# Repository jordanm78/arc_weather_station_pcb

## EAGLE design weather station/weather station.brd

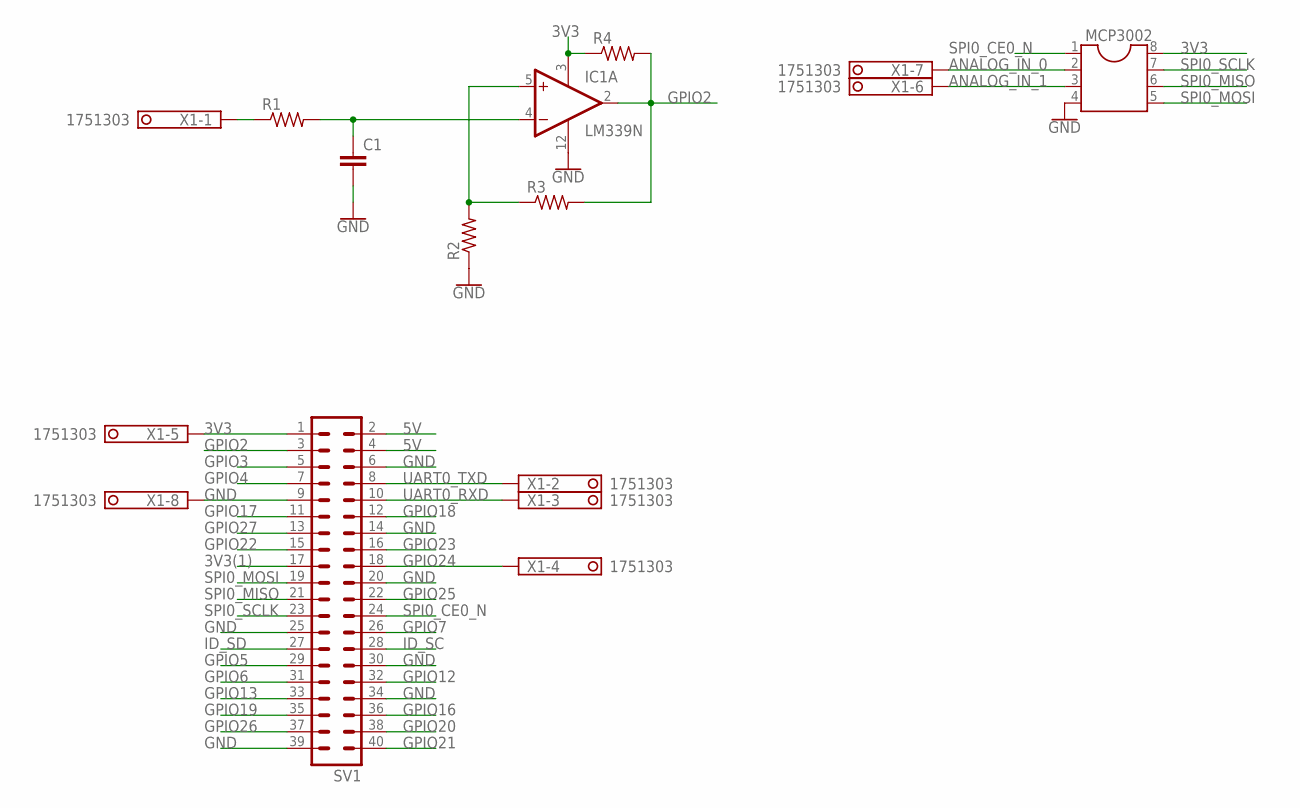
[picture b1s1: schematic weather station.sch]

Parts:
C1: C7.5/4; C7.5B4
IC1: LM339N; DIL14
MCP3002: DIL8S; SOCKET-08
R1, R2, R3, R4: R-US_0207/10; 0207/10
SV1: MA20-2
X1: 1751303

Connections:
3V3: IC1.3 (V+), MCP3002.8, R4.1, SV1.1, X1.5
3V3(1): SV1.17
5V: SV1.2, SV1.4
ANALOG_IN_0: MCP3002.2, X1.7
ANALOG_IN_1: MCP3002.3, X1.6
GND: C1.2, IC1.12 (GND), MCP3002.4, R2.1, SV1.6, SV1.9, SV1.14, SV1.20, SV1.25, SV1.30, SV1.34, SV1.39, X1.8
GPIO2: IC1.2 (OUT), R3.2, R4.2, SV1.3
GPIO3: SV1.5
GPIO4: SV1.7
GPIO5: SV1.29
GPIO6: SV1.31
GPIO7: SV1.26
GPIO12: SV1.32
GPIO13: SV1.33
GPIO16: SV1.36
GPIO17: SV1.11
GPIO18: SV1.12
GPIO19: SV1.35
GPIO20: SV1.38
GPIO21: SV1.40
GPIO22: SV1.15
GPIO23: SV1.16
GPIO24: SV1.18, X1.4
GPIO25: SV1.22
GPIO26: SV1.37
GPIO27: SV1.13
ID_SC: SV1.28
ID_SD: SV1.27
unnamed: C1.1, IC1.4 (-IN), R1.2
unnamed: IC1.5 (+IN), R2.2, R3.1
unnamed: R1.1, X1.1
SPI0_CE0_N: MCP3002.1, SV1.24
SPI0_MISO: MCP3002.6, SV1.21
SPI0_MOSI: MCP3002.5, SV1.19
SPI0_SCLK: MCP3002.7, SV1.23
UART0_RXD: SV1.10, X1.3
UART0_TXD: SV1.8, X1.2

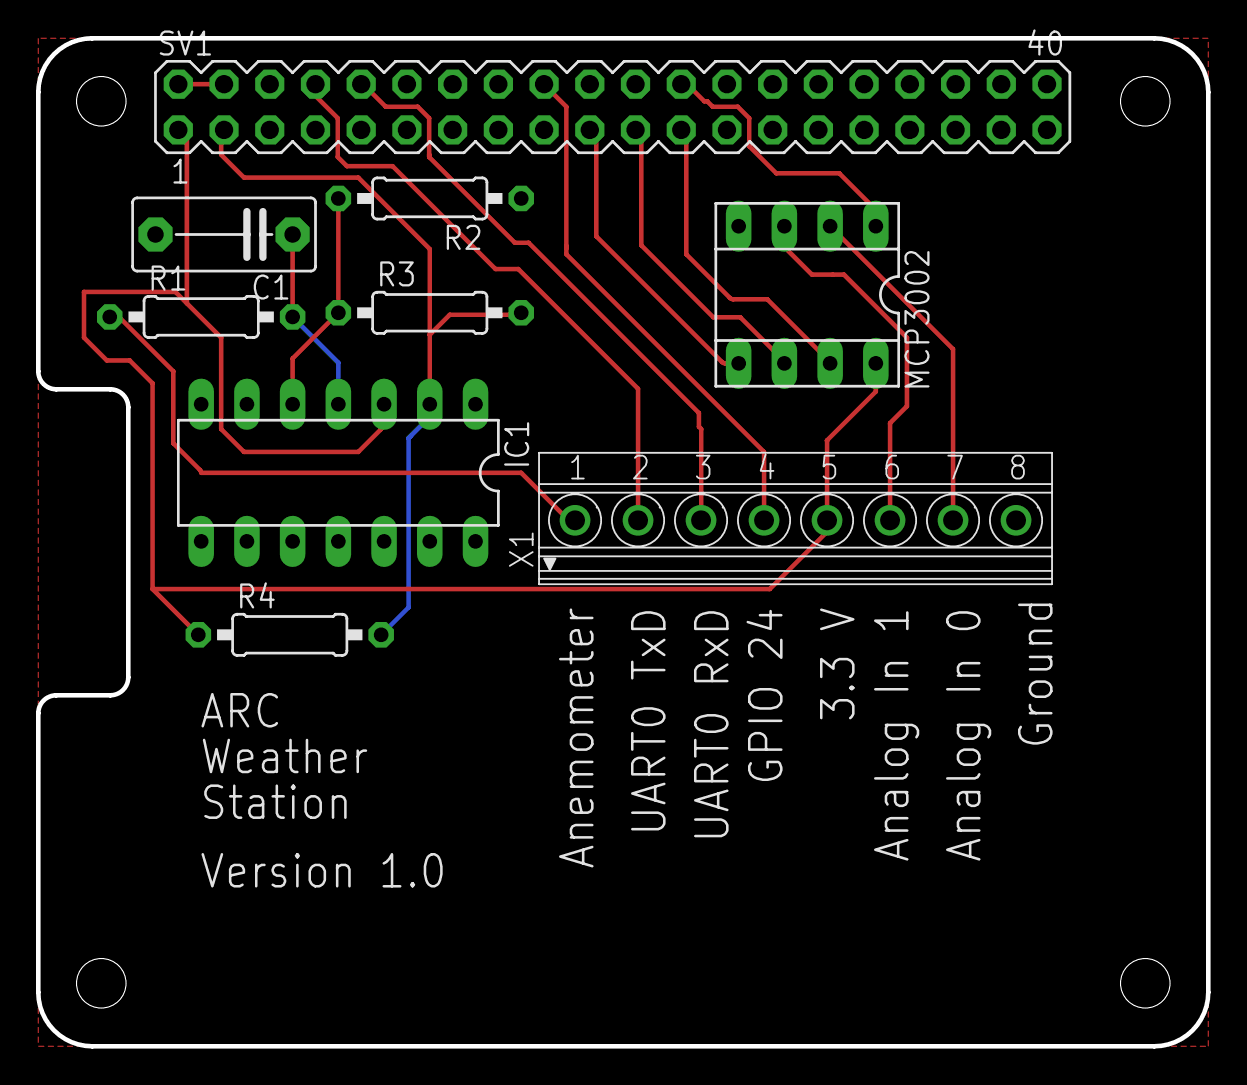
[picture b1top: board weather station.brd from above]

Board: 2 copper layers, 65.0 x 56.0 mm, 9 parts (0 on the bottom side), 16 nets.

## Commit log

2017-05-25 Initial commit of weather station printed circuit board, version 1.0

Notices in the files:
parts and their libraries:
SparkFun-PowerSymbols: Licensing: Creative Commons ShareAlike 4.0 International - https://creativecommons.org/licenses/by-sa/4.0
